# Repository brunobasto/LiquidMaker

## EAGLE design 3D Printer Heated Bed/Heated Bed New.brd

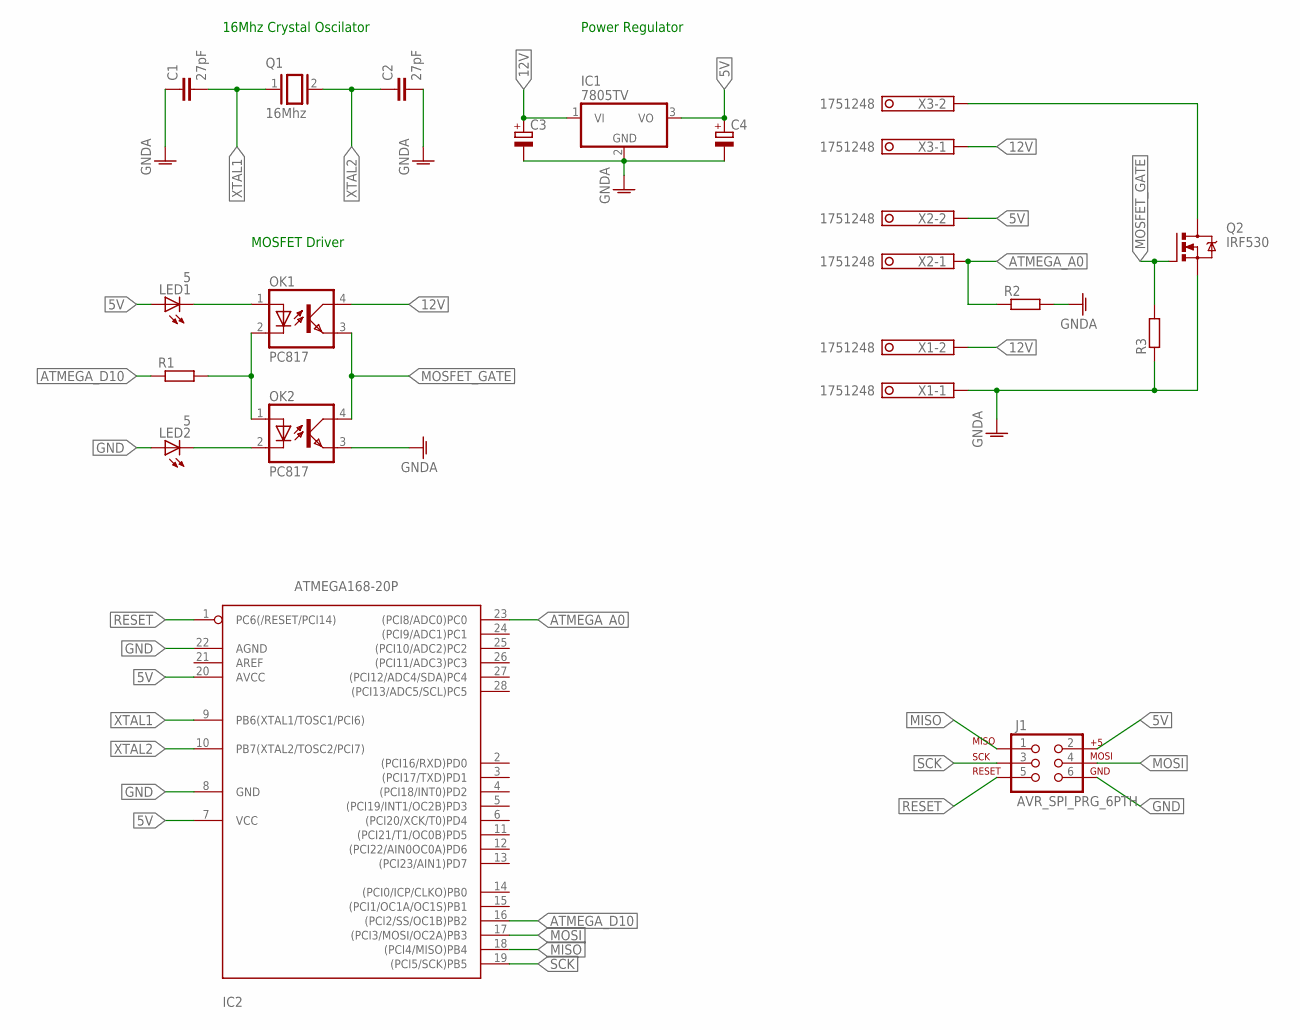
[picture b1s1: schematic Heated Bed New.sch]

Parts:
C1, C2: 27pF; C025-025X050
C3, C4: CPOL-EUE5-10.5; E5-10,5
IC1: 7805TV; TO220V
IC2: ATMEGA168-20P; DIL28-3
J1: AVR_SPI_PRG_6PTH; 2X3
LED1, LED2: 5; LED5MM
OK1, OK2: PC817; DIL04
Q1: 16Mhz; QS
Q2: IRF530; TO220BV
R1, R2, R3: R-EU_0207/7; 0207/7
X1, X2, X3: 1751248

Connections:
5V: C4.+, IC1.3 (VO), IC2.7 (VCC), IC2.20 (AVCC), J1.2, LED1.A, X2.2
12V: C3.+, IC1.1 (VI), OK1.4 (COL), X1.2, X3.1
ATMEGA_A0: IC2.23 ((PCI8/ADC0)PC0), R2.1, X2.1
ATMEGA_D10: IC2.16 ((PCI2/SS/OC1B)PB2), R1.1
GND: C1.1, C2.2, C3.-, C4.-, IC1.2 (GND), IC2.8 (GND), IC2.22 (AGND), J1.6, LED2.A, OK2.3 (EMIT), Q2.S, R2.2, R3.1, X1.1
MISO: IC2.18 ((PCI4/MISO)PB4), J1.1
MOSFET_GATE: OK1.3 (EMIT), OK2.4 (COL), Q2.G, R3.2
MOSI: IC2.17 ((PCI3/MOSI/OC2A)PB3), J1.4
unnamed: LED1.K (C), OK1.1 (A)
unnamed: OK1.2 (C), OK2.1 (A), R1.2
unnamed: LED2.K (C), OK2.2 (C)
unnamed: Q2.D, X3.2
RESET: IC2.1 (PC6(/RESET/PCI14)), J1.5
SCK: IC2.19 ((PCI5/SCK)PB5), J1.3
XTAL1: C1.2, IC2.9 (PB6(XTAL1/TOSC1/PCI6)), Q1.1
XTAL2: C2.1, IC2.10 (PB7(XTAL2/TOSC2/PCI7)), Q1.2

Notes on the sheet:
16Mhz Crystal Oscilator
Power Regulator
MOSFET Driver

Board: 2 copper layers, 19 parts (0 on the bottom side), 16 nets, no tracks yet.

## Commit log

2016-04-29 Fritzing
2016-05-24 Current Limiting
2016-05-24 Gears and Pulleys
2016-05-24 Printable Peristaltic Pump

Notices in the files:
parts and their libraries:
SparkFun-Connectors: Licensing: Creative Commons ShareAlike 4.0 International - https://creativecommons.org/licenses/by-sa/4.0
